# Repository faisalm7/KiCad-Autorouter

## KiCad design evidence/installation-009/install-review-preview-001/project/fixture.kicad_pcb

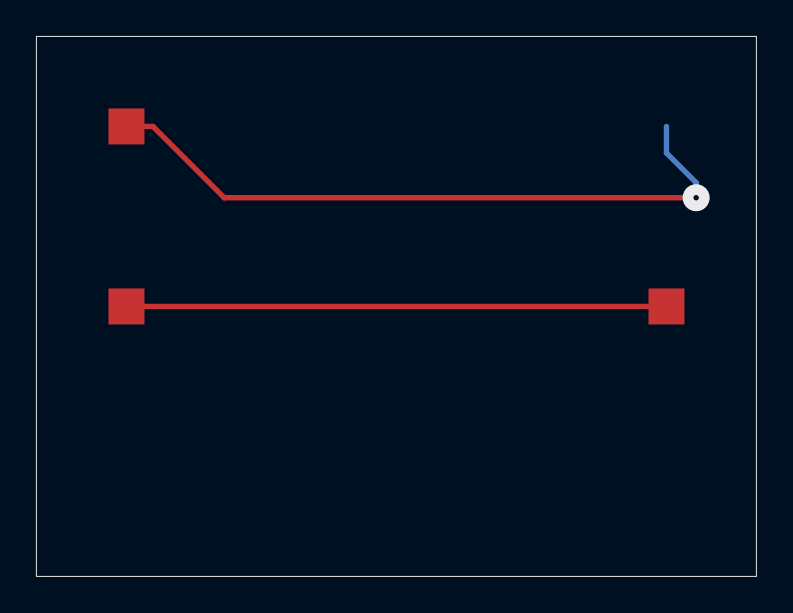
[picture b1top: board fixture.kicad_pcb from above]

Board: 2 copper layers, 40.0 x 30.0 mm, 4 parts (1 on the bottom side), 2 nets.

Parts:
J1, J2, J3, J4: floor_control_terminal

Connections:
SIGNAL_A: J1.1, J2.1
SIGNAL_B: J3.1, J4.1

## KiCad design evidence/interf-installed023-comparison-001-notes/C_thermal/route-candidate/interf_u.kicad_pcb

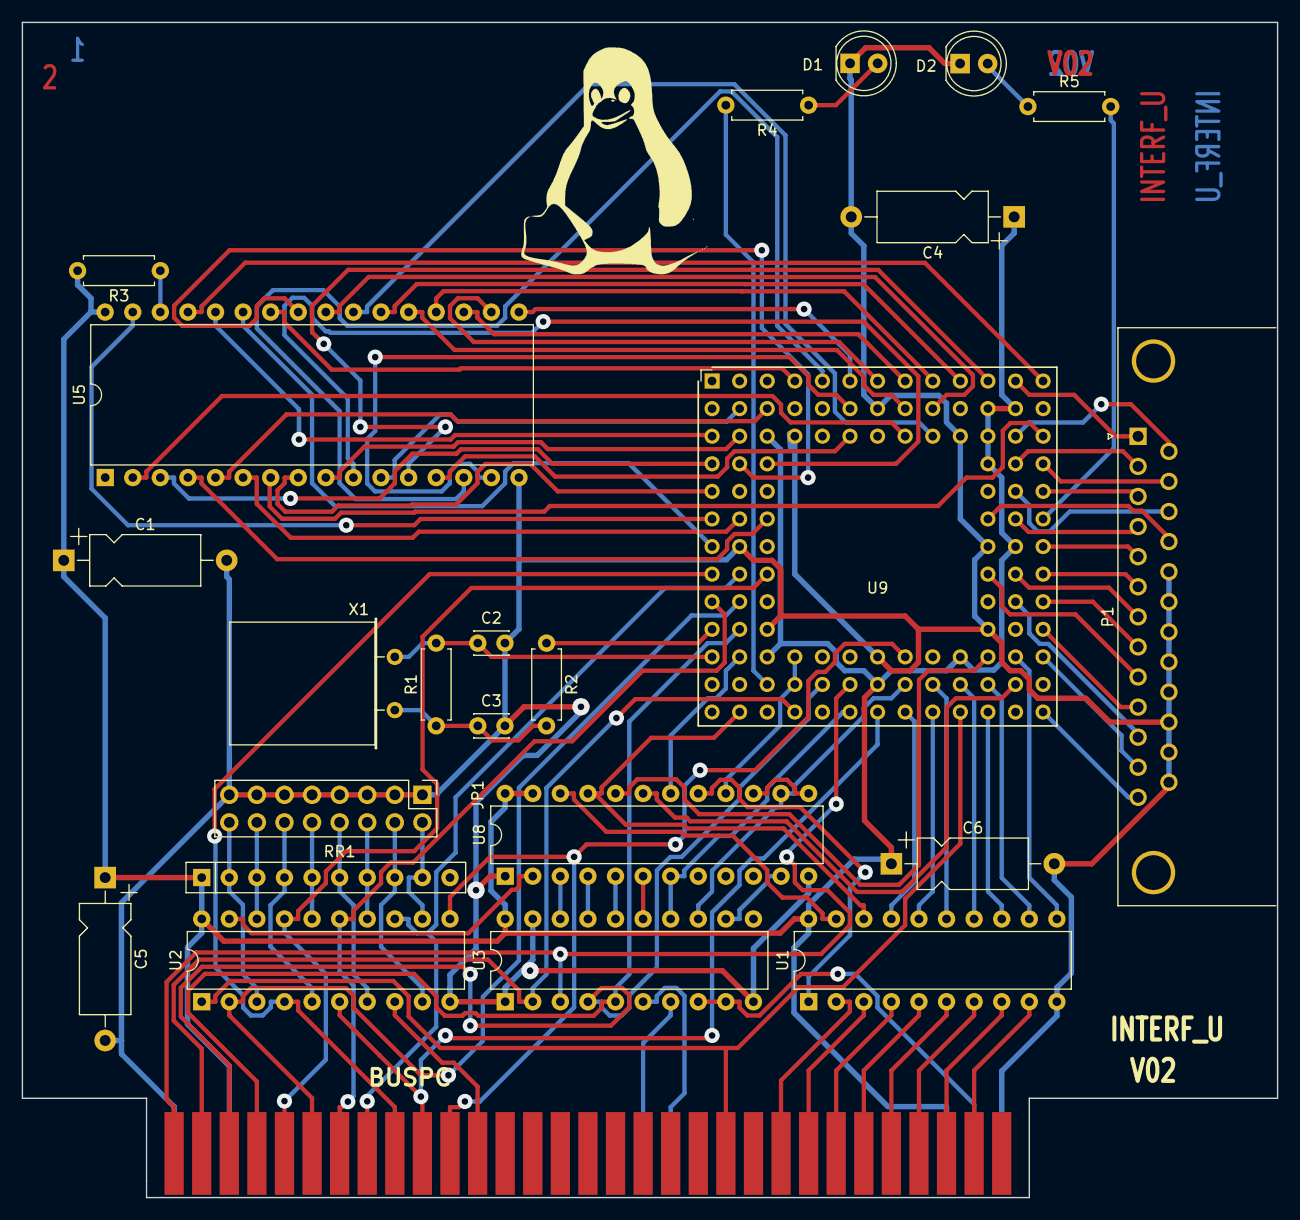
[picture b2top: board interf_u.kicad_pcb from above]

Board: 2 copper layers, 115.6 x 108.2 mm, 25 parts (0 on the bottom side), 110 nets.

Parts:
BUS1: BUSPC; BUS_PC
C1, C4, C5, C6: 47uF; CP_Axial_L10.0mm_D4.5mm_P15.00mm_Horizontal
C2, C3: 47pF; C_Disc_D3.0mm_W2.0mm_P2.50mm
D1, D2: LED; LED_D5.0mm
G1: LOGO; tux
JP1: CONN_8X2; PinHeader_2x08_P2.54mm_Vertical
P1: DB25FEMELLE; DSUB-25_Female_Horizontal_P2.77x2.84mm_EdgePinOffset9.90mm_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
R1: 100K; R_Axial_DIN0207_L6.3mm_D2.5mm_P7.62mm_Horizontal
R2: 1K; R_Axial_DIN0207_L6.3mm_D2.5mm_P7.62mm_Horizontal
R3: 10K; R_Axial_DIN0207_L6.3mm_D2.5mm_P7.62mm_Horizontal
R4, R5: 330; R_Axial_DIN0207_L6.3mm_D2.5mm_P7.62mm_Horizontal
RR1: 9x1K; R_Array_SIP10
U1: 74LS245; DIP-20_W7.62mm
U2: 74LS688; DIP-20_W7.62mm
U3: 74LS541; DIP-20_W7.62mm
U5: 628128; DIP-32_W15.24mm
U8: EP600; DIP-24_W7.62mm
U9: 4003APG120; PGA120
X1: 8MHz; Crystal_HC18-U_Horizontal

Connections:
/8MH-OUT: R2.1, U9.K1 (P/A5)
/ACK: P1.10, U9.K13
/AUTOFD-: P1.14, U9.C12 (PGCK2)
/BIT0: P1.2, U9.D12
/BIT1: P1.3, U9.E13
/BIT2: P1.4, U9.F12
/BIT3: P1.5, U9.G13
/BIT4: P1.6, U9.H13
/BIT5: P1.7, U9.H12
/BIT6: P1.8, U9.J13
/BIT7: P1.9, U9.H11
/BUST+: P1.11, U9.J12
/CLKLCA: U8.16 (I/O16), U9.L4 (CCLK), U9.M4 (NC)
/CS1-: U5.22 (CS1), U9.A10
/D0: U1.18 (B0), U8.21 (I/O21), U9.N2 (DIN)
/D1: U1.17 (B1), U9.N8
/D2: U1.16 (B2), U9.N9
/D3: U1.15 (B3), U9.M9 (P/D5)
/D4: U1.14 (B4), U9.M10 (P/D6)
/D5: U1.13 (B5), U9.N11
/D6: U1.12 (B6), U9.M11 (P/D7)
/D7: U1.11 (B7), U9.L12 (SGCK3)
/DIR: U1.1 (A->B), U8.17 (I/O17)
/DONE: U8.20 (I/O20), U9.L11 (DONE)
/ENBBUF: U1.19 (CE), U8.22 (I/O22)
/ERROR-: P1.15, U9.D13
/INIT-: P1.16, U9.E12
/LED1: R4.2, U9.M3 (DOUT-SGKC4)
/LED2: R5.2, U9.F13 (INIT)
/MA0: U5.12 (A0), U9.A11
/MA1: U5.11 (A1), U9.B2 (PGCK1/A16)
/MA2: U5.10 (A2), U9.D3 (SGCK1)
/MA3: U5.9 (A3), U9.C2 (P/A14)
/MA4: U5.8 (A4), U9.E1
/MA5: U5.7 (A5), U9.C13 (LDC)
/MA6: U5.6 (A6), U9.F2
/MA7: U5.5 (A7), U9.B3 (P/A17)
/MA8: U5.27 (A8), U9.G1 (P/A8)
/MA9: U5.26 (A9), U9.A4
/MA10: U5.23 (A10), U9.C9
/MA11: U5.25 (A11), U9.D2 (P/A13)
/MA12: U5.4 (A12), U9.F3 (P/A10)
/MA13: U5.28 (A13), U9.C1 (P/A12)
/MA14: U5.3 (A14), U9.D1 (P/A11)
/MA15: U5.31 (A15), U9.F1 (P/A9)
/MA16: U5.2 (A16), U9.C8
/MATCHL: U2.19 (P=R), U8.2 (IN2)
/MD0: U5.13 (Q0), U9.C6
/MD1: U5.14 (Q1), U9.A5
/MD2: U5.15 (Q2), U9.B6
/MD3: U5.17 (Q3), U9.A6
/MD4: U5.18 (Q4), U9.A7
/MD5: U5.19 (Q5), U9.A8
/MD6: U5.20 (Q6), U9.A9
/MD7: U5.21 (Q7), U9.B8
/OE-: U5.24 (OE), U9.B9
/PC-A0: BUS1.62 (BA00), U3.3 (A1), U9.M6
/PC-A1: BUS1.61 (BA01), U3.2 (A0), U9.N4
/PC-A2: BUS1.60 (BA02), U3.4 (A2), U9.M5 (P/D1)
/PC-A3: BUS1.59 (BA03), U3.5 (A3), U9.K2 (P/CS1/A2)
/PC-A4: BUS1.58 (BA04), U2.17 (P7), U9.H3
/PC-A5: BUS1.57 (BA05), U2.2 (P0), U9.J2 (P/A4)
/PC-A6: BUS1.56 (BA06), U2.15 (P6), U9.J1
/PC-A7: BUS1.55 (BA07), U2.13 (P5), U9.H2 (P/A6)
/PC-A8: BUS1.54 (BA08), U2.4 (P1), U9.H1 (P/A7)
/PC-A9: BUS1.53 (BA09), U2.6 (P2), U9.N7 (P/D3)
/PC-A10: BUS1.52 (BA10), U2.11 (P4), U9.L8
/PC-A11: BUS1.51 (BA11), U2.8 (P3)
/PC-AEN: BUS1.42 (AEN), U2.1 (G), U9.N10 (P/CS0)
/PC-DB0: BUS1.40 (DB0), U1.2 (A0)
/PC-DB1: BUS1.39 (DB1), U1.3 (A1)
/PC-DB2: BUS1.38 (DB2), U1.4 (A2)
/PC-DB3: BUS1.37 (DB3), U1.5 (A3)
/PC-DB4: BUS1.36 (DB4), U1.6 (A4)
/PC-DB5: BUS1.35 (DB5), U1.7 (A5)
/PC-DB6: BUS1.34 (DB6), U1.8 (A6)
/PC-DB7: BUS1.33 (DB7), U1.9 (A7)
/PC-IOR: BUS1.14 (IOR), U3.7 (A5)
/PC-IOW: BUS1.13 (IOW), U3.6 (A4)
/PC-RD: U3.13 (Y5), U8.14 (IN14), U9.M8 (P/D4)
/PC-RST: BUS1.2 (RESET), U3.8 (A6), U3.9 (A7)
/PC-WR: U3.14 (Y4), U8.7 (I/O7), U9.N6 (P/RS)
/PE+: P1.12, U9.L13
/PROG-: U8.19 (I/O19), U9.M12 (PROG)
/REF4: JP1.14, RR1.3, U2.18 (R7)
/REF5: JP1.16, RR1.2, U2.3 (R0)
/REF6: JP1.10, RR1.5, U2.16 (R6)
/REF7: JP1.6, RR1.7, U2.14 (R5)
/REF8: JP1.12, RR1.4, U2.5 (R1)
/REF9: JP1.8, RR1.6, U2.7 (R2)
/REF10: JP1.2, RR1.9, U2.12 (R4)
/REF11: JP1.4, RR1.8, U2.9 (R3)
/RSTL: U3.12 (Y6), U8.11 (IN11)
/SEL_LPT: U8.18 (I/O18), U9.L2 (P/A0/WS)
/SLCT+: P1.13, U9.N13 (PGCK3)
/SLCTIN-: P1.17, U9.F11
/STROBE: P1.1, U9.A12 (SGCK2)
/WR-: U5.29 (WR), U9.A13 (HDC)
/WR_REG: U8.13 (CLK2), U8.15 (I/O15)
GND: BUS1.1 (GND), BUS1.31 (GND), C1.2, C2.2, C3.2, C4.2, C5.2, C6.2, D1.1 (K), D2.1 (K), JP1.1, JP1.3, JP1.5, JP1.7, JP1.9, JP1.11, JP1.13, JP1.15, P1.18, P1.19, P1.20, P1.21, P1.22, P1.23, P1.24, P1.25, U1.10 (GND), U2.10 (GND), U3.1 (G1), U3.10 (GND), U3.19 (G2), U5.16 (GND), U8.1 (CLK1), U8.12 (GND), U9.B7 (GND), U9.C4 (GND), U9.C10 (GND), U9.G2 (GND), U9.G11 (GND), U9.K3 (GND), U9.K11 (GND), U9.L7 (GND)
unnamed: C3.1, R1.1, R2.2, X1.2
unnamed: D1.2 (A), R4.1
unnamed: D2.2 (A), R5.1
unnamed: U3.18 (Y0), U8.3 (I/O3)
unnamed: U3.17 (Y1), U8.4 (I/O4)
unnamed: U3.16 (Y2), U8.5 (I/O5)
unnamed: U3.15 (Y3), U8.6 (I/O6)
unnamed: R3.1, U5.30 (CS2)
unnamed: C2.1, R1.2, U9.L1 (P/A3), X1.1
VCC: BUS1.3 (VCC), BUS1.29 (VCC), C1.1, C4.1, C5.1, C6.1, R3.2, RR1.1 (COM), U1.20 (VCC), U2.20 (VCC), U3.20 (VCC), U5.32 (VCC), U8.23 (IN23), U8.24 (VCC), U9.B11 (M1), U9.B12 (M2), U9.C3 (VCC), U9.C11 (M0), U9.D11 (VCC), U9.G12 (VCC), U9.L3 (VCC), U9.L10 (VCC), U9.M7 (VCC)
